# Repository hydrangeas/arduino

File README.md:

arduino
=======

## 利用方法

+ SleepClock/SleepClock.inoを立ち上げると他はタブとして読み込まれる

「タブ」とはArduino用語で、メイン（setup/loop）以外に分割されたファイルの
ことをいいます。

## 解析

+ SleepClockData.shでSDカードから書式にマッチしたデータだけを抽出します
+ SleepClockPlot.shでグラフを出力します

`SleepClockData.sh`内に`totalPer1min`と記述されている箇所があり、
そこで１分毎にデータを集計しています。
`totalPer1sec`と`totalPer10sec`はそれぞれ1秒毎、10秒毎に集計できます。

`SleepClockPlot.sh`は内部でGnuplotを使用していますので、
これがない場合はエラーとなり、終了します。
必ず、このシェルが参照できる場所にパスを通しておいてください （検索まではしません）。

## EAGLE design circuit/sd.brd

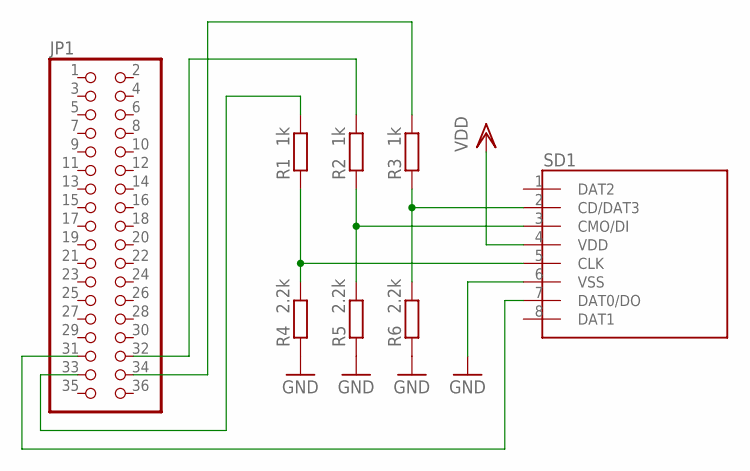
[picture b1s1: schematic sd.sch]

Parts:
JP1: PINHD-2X18; 2X18
R1, R2, R3: 1k; 0204V
R4, R5, R6: 2.2k; 0204V
SD1: CK-40; SD

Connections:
GND: R4.1, R5.1, R6.1, SD1.6 (VSS)
unnamed: R3.1, R6.2, SD1.2 (CD/DAT3)
unnamed: R2.1, R5.2, SD1.3 (CMO/DI)
unnamed: R1.1, R4.2, SD1.5 (CLK)
unnamed: JP1.32, R2.2
unnamed: JP1.34, R3.2
unnamed: JP1.33, R1.2
unnamed: JP1.31, SD1.7 (DAT0/DO)
VDD: SD1.4 (VDD)

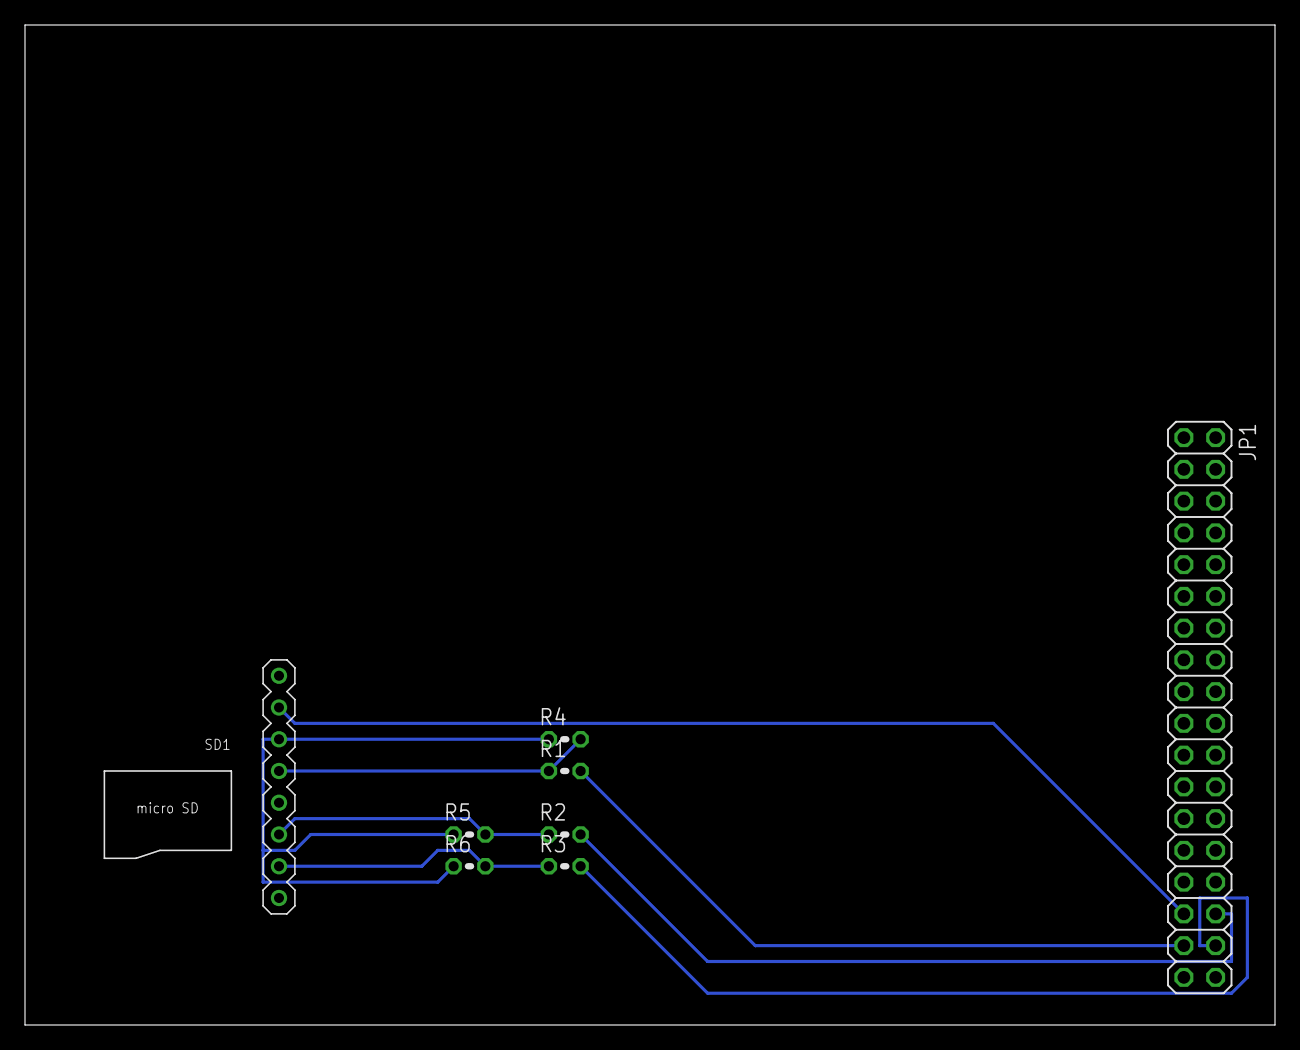
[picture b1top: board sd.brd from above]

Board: 2 copper layers, 100.0 x 80.0 mm, 8 parts (0 on the bottom side), 8 nets.

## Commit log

2013-02-01 copied templates
2013-02-01 minimum sentences
2013-02-01 change index
2013-02-02 add circuit files
2013-02-04 first complete
2013-02-04 move changes to my csses from css3-github-buttons module
2013-02-04 disable links for future projects
2013-02-04 add google trancking codes
2021-05-02 Set theme jekyll-theme-minimal
